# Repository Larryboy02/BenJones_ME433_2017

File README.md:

Author: Ben Jones
Date first created: 03/28/17, 18:19

This repository will be a folder for all documents, images, and code pertaining to ME 333.
The repo's subfolders are organized by homework (e.g. HW1, HW2, etc).
The final project will be organized in its own folder at a later date. 

This is a dummy line to make sure that changes are reflected in GitHub commits.

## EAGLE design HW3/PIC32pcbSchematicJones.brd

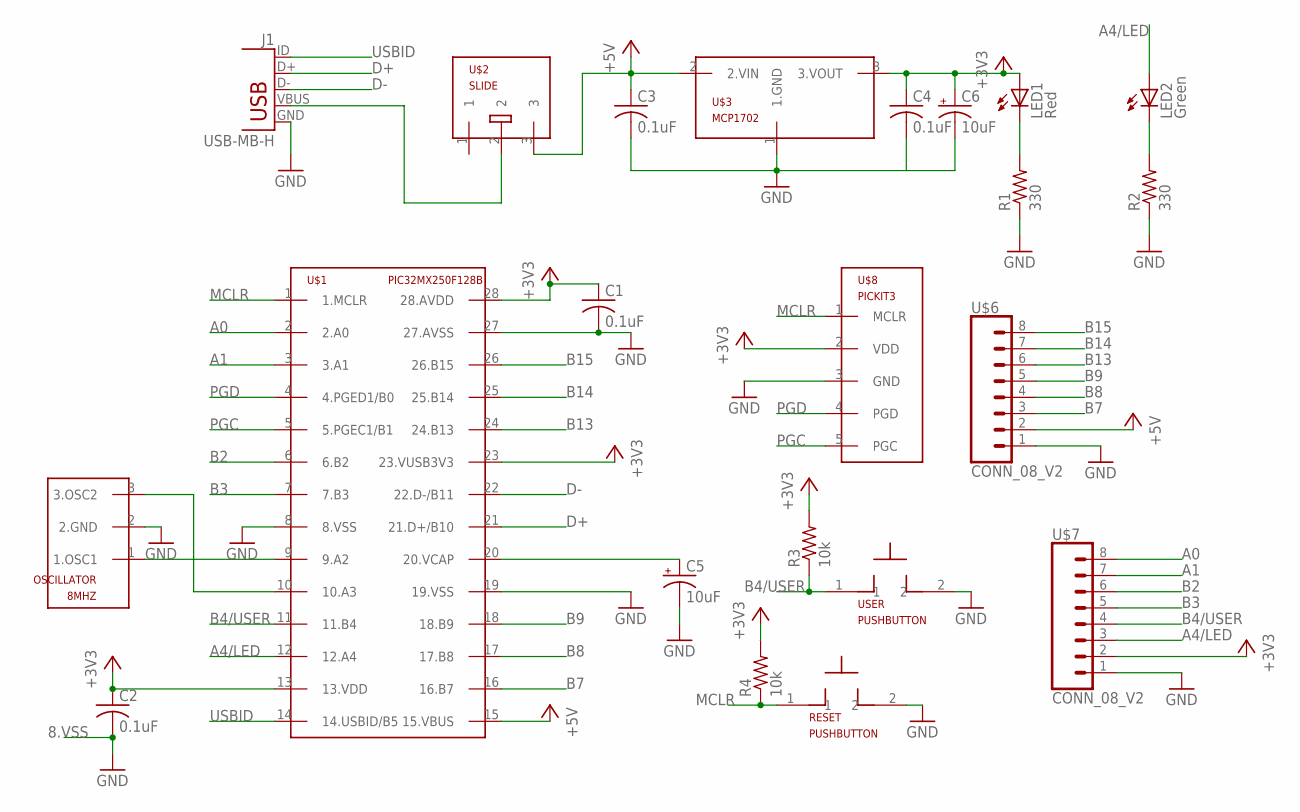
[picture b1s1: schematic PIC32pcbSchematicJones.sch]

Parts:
8MHZ: OSCILLATOR
C1, C2, C3, C4: 0.1uF; C025-025X050
C5, C6: 10uF; B45181B
J1: USB-MB-H
LED1: Red; LED3MM
LED2: Green; LED3MM
R1, R2: 330; 0207/10
R3, R4: 10k; 0207/10
RESET: PUSHBUTTON
U$1: PIC32MX250F128B; DIL28-3
U$2: SLIDE
U$3: MCP1702; TO92
U$6, U$7: CONN_08_V2; 1X08
U$8: PICKIT3; 1X05
USER: PUSHBUTTON

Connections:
8.VSS: C2.2
+3V3: C1.1, C2.1, C4.1, C6.+, LED1.A, R3.2, R4.2, U$1.13 (13.VDD), U$1.23 (23.VUSB3V3), U$1.28 (28.AVDD), U$3.3 (3.VOUT), U$7.2, U$8.2 (VDD)
+5V: C3.1, U$1.15 (15.VBUS), U$2.3, U$3.2 (2.VIN), U$6.2
A0: U$1.2 (2.A0), U$7.8
A1: U$1.3 (3.A1), U$7.7
A4/LED: LED2.A, U$1.12 (12.A4), U$7.3
B2: U$1.6 (6.B2), U$7.6
B3: U$1.7 (7.B3), U$7.5
B4/USER: R3.1, U$1.11 (11.B4), U$7.4, USER.1
B7: U$1.16 (16.B7), U$6.3
B8: U$1.17 (17.B8), U$6.4
B9: U$1.18 (18.B9), U$6.5
B13: U$1.24 (24.B13), U$6.6
B14: U$1.25 (25.B14), U$6.7
B15: U$1.26 (26.B15), U$6.8
D+: J1.D+, U$1.21 (21.D+/B10)
D-: J1.D-, U$1.22 (22.D-/B11)
GND: 8MHZ.2 (2.GND), C1.2, C3.2, C5.-, C6.-, J1.GND, R1.1, R2.1, RESET.2, U$1.8 (8.VSS), U$1.19 (19.VSS), U$1.27 (27.AVSS), U$3.1 (1.GND), U$6.1, U$7.1, U$8.3 (GND), USER.2
MCLR: R4.1, RESET.1, U$1.1 (1.MCLR), U$8.1 (MCLR)
unnamed: LED2.K (C), R2.2
unnamed: 8MHZ.1 (1.OSC1), U$1.9 (9.A2)
unnamed: 8MHZ.3 (3.OSC2), U$1.10 (10.A3)
unnamed: C5.+, U$1.20 (20.VCAP)
unnamed: LED1.K (C), R1.2
PGC: U$1.5 (5.PGEC1/B1), U$8.5 (PGC)
PGD: U$1.4 (4.PGED1/B0), U$8.4 (PGD)
USBID: J1.ID, U$1.14 (14.USBID/B5)
VBUS: J1.VBUS, U$2.2

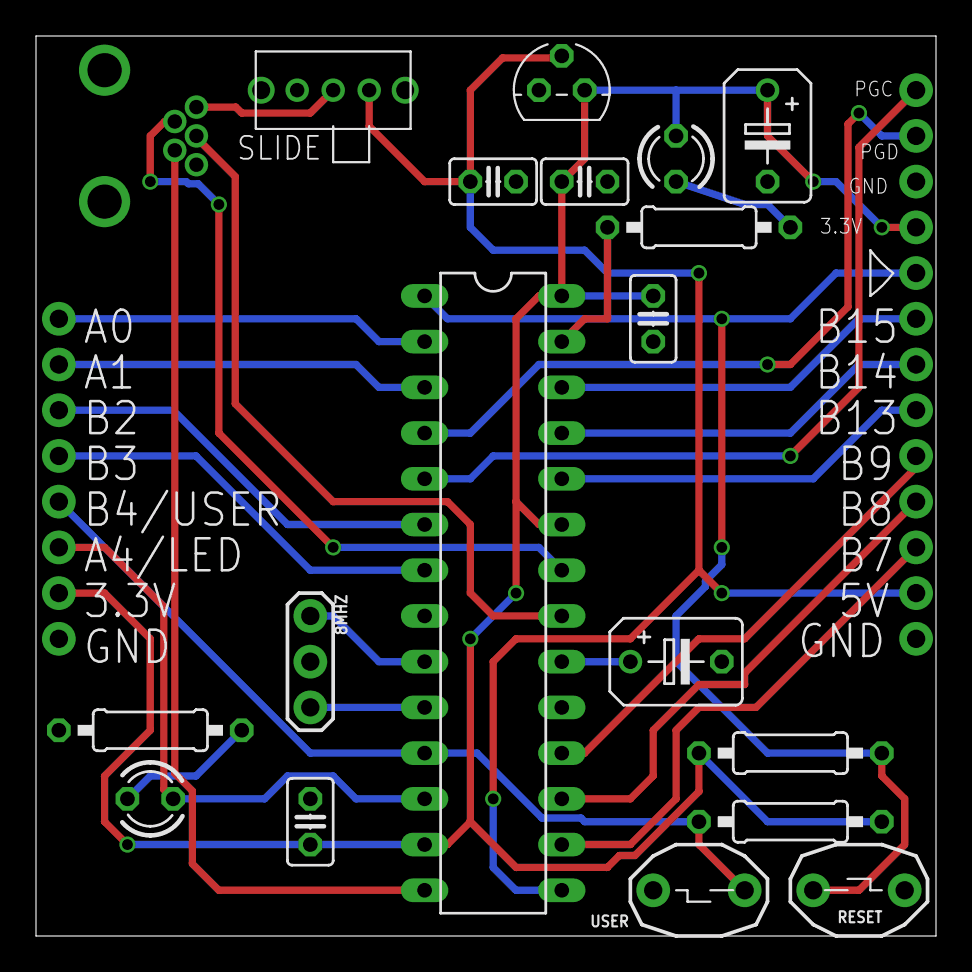
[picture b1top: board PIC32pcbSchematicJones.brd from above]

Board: 2 copper layers, 50.0 x 50.0 mm, 22 parts (0 on the bottom side), 27 nets.

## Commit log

2017-03-28 :boom::camel: Added .gitattributes
2017-03-28 My first commit, README!
2017-03-28 Added dummy line at end.
2017-03-28 Problem 1 complete
    Add photo of circuit diagram (including Pololu USB-B minibreakout,
    MCP1702 voltage regulator, PICkit3 programmer, PIC32MX250F128B, 8MHz
    crystal resonator)
2017-03-29 Photos of Problems 2-6 complete
2017-03-29 Created HW1.X folder for main.c.
    Pictures moved from HW1 to HW1.X\pictures. HW1 deleted. Main.c created
    in MPLABX IDE.
2017-03-30 Updated main.c to include all pragma values
2017-03-30 Main.c: Added pins A4 and B4 TRIS. Set A4 high before infinite loop
2017-03-30 Added infinite while loop to test timing (1 kHz LED)
2017-03-30 Added loop to read pushbutton and turn off LED if pushed.
2017-03-30 Took demo video of intended main.c function
2017-04-04 Built schematic and library according to demo vids.
    Board file started but hardly worked on at all.
2017-04-06 Built board, generated Gerber files.
2017-04-06 Moved files from old computer to new one.
2017-04-11 Started SPI comm. Totally lost.
2017-04-11 Tried to update functions.
2017-04-11 added circuit diagram jpg
2017-04-13 Wrote code for HW5. No debugging yet.
2017-04-13 Got errors re octal constants in functions accessing registers
    Does not like syntax "09h" (as presented in MCP23008 datasheet), "09",
    or "009". Throws error " main.c:103:21: error: invalid digit "9" in
    octal constant "
2017-04-13 Changed "octal" values to hex, still errors.
    Error: "collect2.exe: error: ld returned 255 exit status"
2017-04-13 Compiling successful, PICkit3 failed.
    Text displayed:
    Connecting to MPLAB PICkit 3...
    Currently loaded firmware on PICkit 3
    Firmware Suite Version.....01.47.12
    Firmware type..............PIC32MX
    Target voltage detected
2017-04-13 Added functions explicitly into main.c; tried changing baud rate to hex (no effect)
2017-04-13 Added built-circuit photo
2017-04-13 added comment to main re adding pullup resistors
2017-04-13 Tried using IPE (instead of IDE) to program w/ PICkit; failed
